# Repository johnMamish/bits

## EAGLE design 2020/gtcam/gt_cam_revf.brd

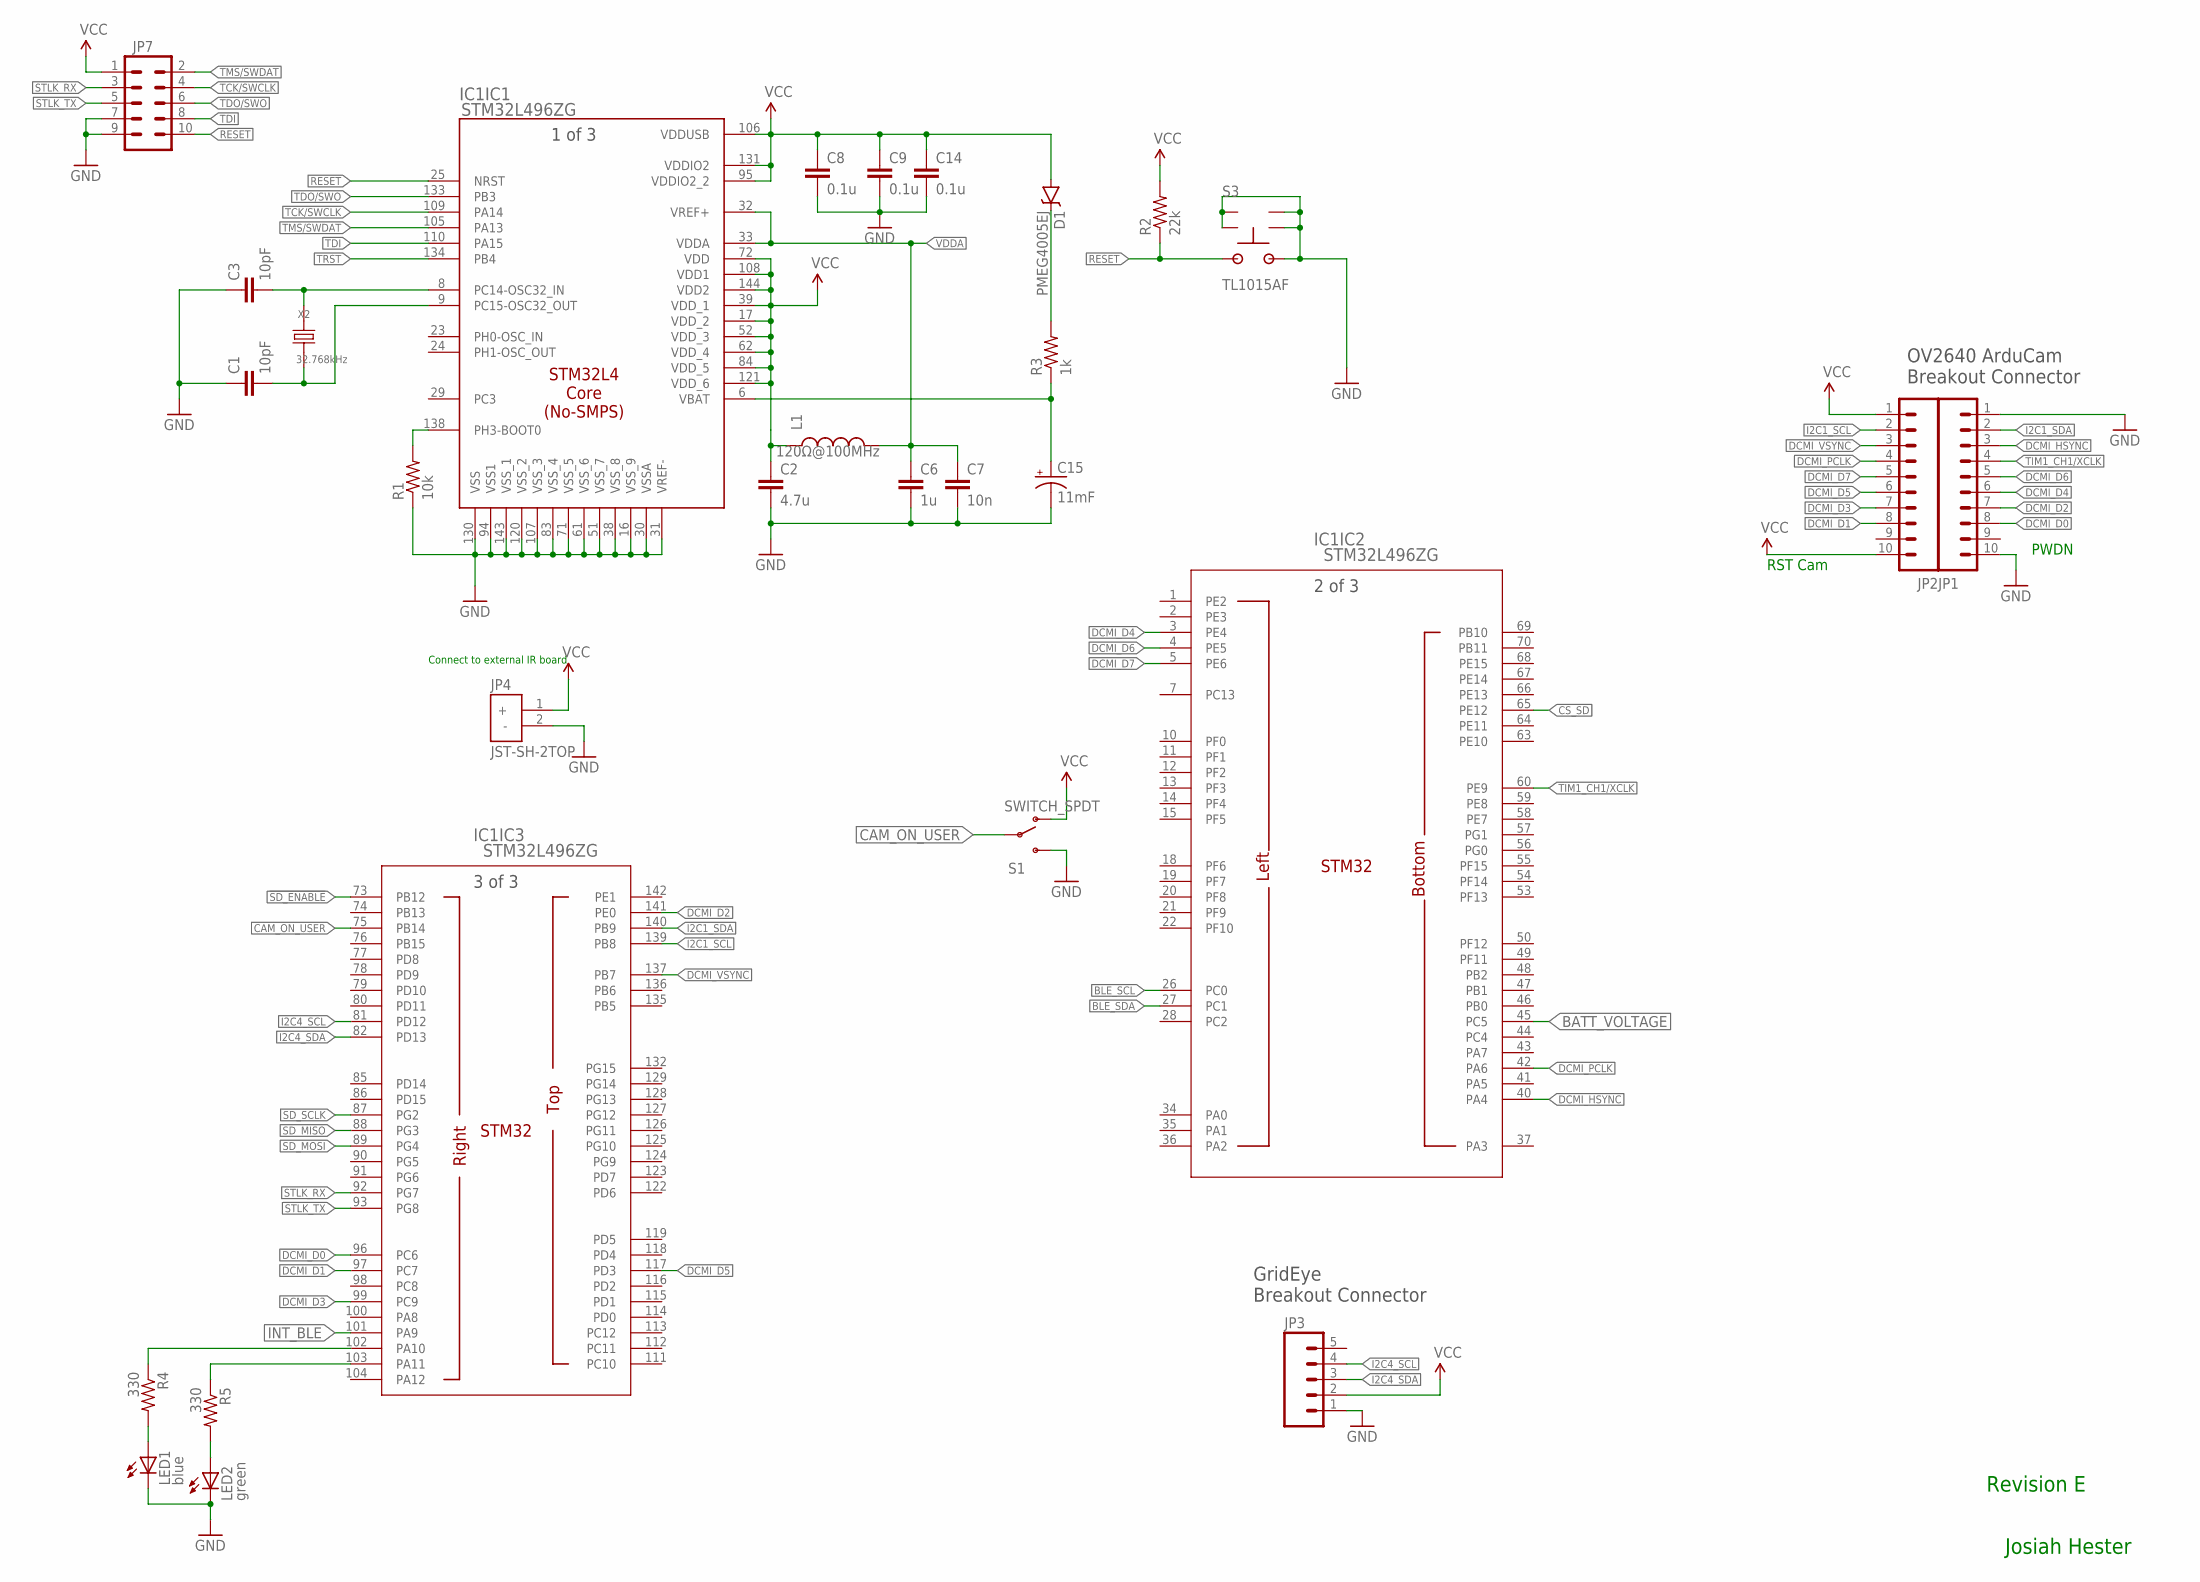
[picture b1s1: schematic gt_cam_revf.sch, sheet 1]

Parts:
C1, C3: 10pF; 0603
C2: 4.7u; 0805
C6: 1u; 0603
C7: 10n; 0603
C8, C9, C14: 0.1u; 0603
C15: 11mF; EIA3216; DIGIKEY 728-1067-1-ND
D1: PMEG4005EJ; SOD-323
IC1: STM32L496ZG; LQFP144-20X20MM; DIGIKEY 497-17999-ND
JP1, JP2: M10SILK_FEMALE_PTH; 1X10
JP3: M05LOCK; 1X05_LOCK
JP4: JST-SH-2TOP; JST-SH-2-TOP
JP7: M05X21.27MM; 2X5_1.27MM; DIGIKEY 1175-1627-ND
L1: 120Ω@100MHz; 0402; DIGIKEY 490-4000-1-ND
LED1: blue; LED-0603
LED2: green; LED-0603
R1: 10k; 0603
R2: 22k; 0603
R3: 1k; 0603
R4, R5: 330; 0603
S1: SWITCH_SPDT; EG-1213
S3: TL1015AF; TS1015; MPN TL1015AF160QG
X2: 32.768kHz; FC-135_1PRIMARY

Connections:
!CS_SD: IC1.65 (PE12); also elsewhere on the board
!SD_ENABLE: IC1.73 (PB12); also elsewhere on the board
BATT_VOLTAGE: IC1.45 (PC5); also elsewhere on the board
BLE_SCL: IC1.26 (PC0); also elsewhere on the board
BLE_SDA: IC1.27 (PC1); also elsewhere on the board
CAM_ON_USER: IC1.75 (PB14), S1.C
DCMI_D0: IC1.96 (PC6), JP1.8
DCMI_D1: IC1.97 (PC7), JP2.8
DCMI_D2: IC1.141 (PE0), JP1.7
DCMI_D3: IC1.99 (PC9), JP2.7
DCMI_D4: IC1.3 (PE4), JP1.6
DCMI_D5: IC1.117 (PD3), JP2.6
DCMI_D6: IC1.4 (PE5), JP1.5
DCMI_D7: IC1.5 (PE6), JP2.5
DCMI_HSYNC: IC1.40 (PA4), JP1.3
DCMI_PCLK: IC1.42 (PA6), JP2.4
DCMI_VSYNC: IC1.137 (PB7), JP2.3
GND: C1.1, C2.2, C3.1, C6.2, C7.2, C8.2, C9.2, C14.2, C15.C (-), IC1.16 (VSS_9), IC1.30 (VSSA), IC1.31 (VREF-), IC1.38 (VSS_8), IC1.51 (VSS_7), IC1.61 (VSS_6), IC1.71 (VSS_5), IC1.83 (VSS_4), IC1.94 (VSS1), IC1.107 (VSS_3), IC1.120 (VSS_2), IC1.130 (VSS), IC1.143 (VSS_1), JP1.1, JP1.10, JP3.1, JP4.2 (-), JP7.7, JP7.9, LED1.C, LED2.C, R1.1, S1.S, S3.1, S3.G1 (GND), S3.G2 (GND), S3.G3 (GND), S3.G4 (GND); also elsewhere on the board
I2C1_SCL: IC1.139 (PB8), JP2.2
I2C1_SDA: IC1.140 (PB9), JP1.2
I2C4_SCL: IC1.81 (PD12), JP3.4
I2C4_SDA: IC1.82 (PD13), JP3.3
INT_BLE: IC1.101 (PA9); also elsewhere on the board
unnamed: C3.2, IC1.8 (PC14-OSC32_IN), X2.2
unnamed: C1.2, IC1.9 (PC15-OSC32_OUT), X2.1
unnamed: IC1.138 (PH3-BOOT0), R1.2
unnamed: D1.C, R3.2
unnamed: IC1.103 (PA11), R5.1
unnamed: IC1.102 (PA10), R4.1
unnamed: LED1.A, R4.2
unnamed: LED2.A, R5.2
RESET: IC1.25 (NRST), JP7.10, R2.1, S3.2
RTC_VBAT: C15.A (+), IC1.6 (VBAT), R3.1
SD_MISO: IC1.88 (PG3); also elsewhere on the board
SD_MOSI: IC1.89 (PG4); also elsewhere on the board
SD_SCLK: IC1.87 (PG2); also elsewhere on the board
STLK_RX: IC1.92 (PG7), JP7.3
STLK_TX: IC1.93 (PG8), JP7.5
TCK/SWCLK: IC1.109 (PA14), JP7.4
TDI: IC1.110 (PA15), JP7.8
TDO/SWO: IC1.133 (PB3), JP7.6
TIM1_CH1/XCLK: IC1.60 (PE9), JP1.4
TMS/SWDAT: IC1.105 (PA13), JP7.2
TRST: IC1.134 (PB4)
VCC: C2.1, C8.1, C9.1, C14.1, D1.A, IC1.17 (VDD_2), IC1.39 (VDD_1), IC1.52 (VDD_3), IC1.62 (VDD_4), IC1.72 (VDD), IC1.84 (VDD_5), IC1.95 (VDDIO2_2), IC1.106 (VDDUSB), IC1.108 (VDD1), IC1.121 (VDD_6), IC1.131 (VDDIO2), IC1.144 (VDD2), JP2.1, JP2.10, JP3.2, JP4.1 (+), JP7.1, L1.1, R2.2, S1.P (O); also elsewhere on the board
VDDA: C6.1, C7.1, IC1.32 (VREF+), IC1.33 (VDDA), L1.2

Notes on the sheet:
OV2640 ArduCam Breakout Connector
GridEye Breakout Connector
Revision E
Josiah Hester
PWDN
RST Cam
Connect to external IR board

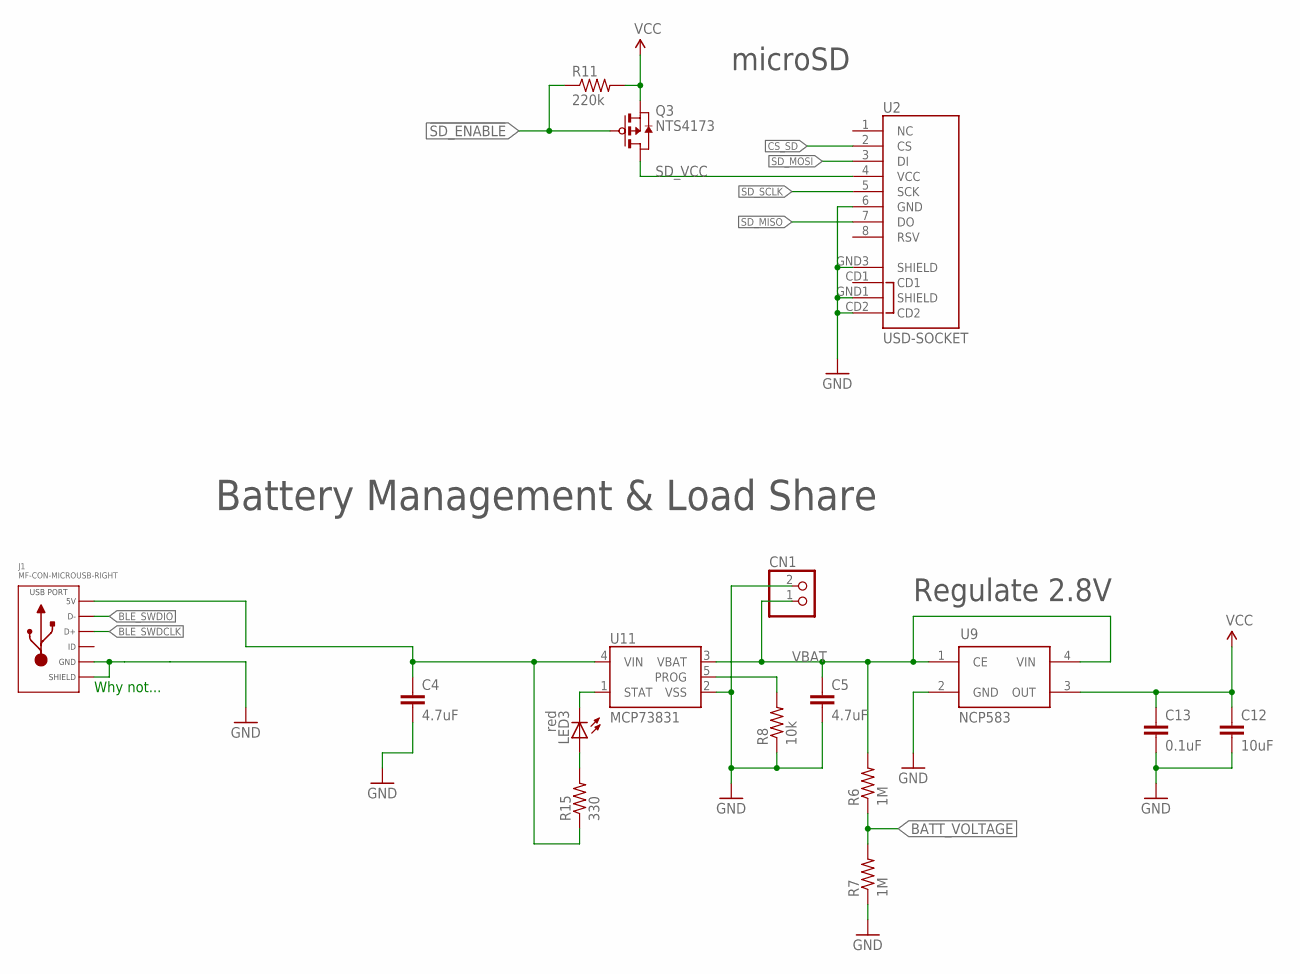
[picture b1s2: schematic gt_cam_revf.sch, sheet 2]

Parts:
C4, C5: 4.7uF; 0805
C12: 10uF; 0805
C13: 0.1uF; 0603
CN1: JST_2PIN-SMT-RA; JST-PH-2-SMT-RA
J1: MF-CON-MICROUSB-RIGHT; MICROUSB-RIGHT
LED3: red; LED-0603
Q3: NTS4173; SC-70-3
R6, R7: 1M; 0603
R8: 10k; 0603
R11: 220k; 0603; DIGIKEY RHM12.0KCDCT-ND
R15: 330; 0603
U2: USD-SOCKET; MICROSD_1:1; DIGIKEY WM3290CT-ND
U9: NCP583; SC82-AB_1PRIMARY
U11: MCP73831; SOT23-5

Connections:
!CS_SD: U2.2 (CS); also elsewhere on the board
!SD_ENABLE: Q3.P1 (G), R11.1; also elsewhere on the board
BATT_VOLTAGE: R6.1, R7.2; also elsewhere on the board
BLE_SWDCLK: J1.3 (D+); also elsewhere on the board
BLE_SWDIO: J1.2 (D-); also elsewhere on the board
GND: C4.2, C5.2, C12.2, C13.2, CN1.2 (1), J1.5 (GND), J1.S1 (SLD), J1.S2 (SLD), J1.S3 (SLD), J1.S4 (SLD), J1.S5 (SLD), J1.S6 (SLD), R7.1, R8.1, U2.6 (GND), U2.CD2, U2.GND1 (SHIELD), U2.GND3 (SHIELD), U9.2 (GND), U11.2 (VSS); also elsewhere on the board
MOB: C4.1, J1.1 (5V), R15.1, U11.4 (VIN)
unnamed: R8.2, U11.5 (PROG)
unnamed: LED3.C, U11.1 (STAT)
unnamed: LED3.A, R15.2
SD_MISO: U2.7 (DO); also elsewhere on the board
SD_MOSI: U2.3 (DI); also elsewhere on the board
SD_SCLK: U2.5 (SCK); also elsewhere on the board
SD_VCC: Q3.P3 (D), U2.4 (VCC)
VBAT: C5.1, CN1.1 (2), R6.2, U9.1 (CE), U9.4 (VIN), U11.3 (VBAT)
VCC: C12.1, C13.1, Q3.P2 (S), R11.2, U9.3 (OUT); also elsewhere on the board

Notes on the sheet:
Regulate 2.8V
Battery Management & Load Share
microSD
Why not...

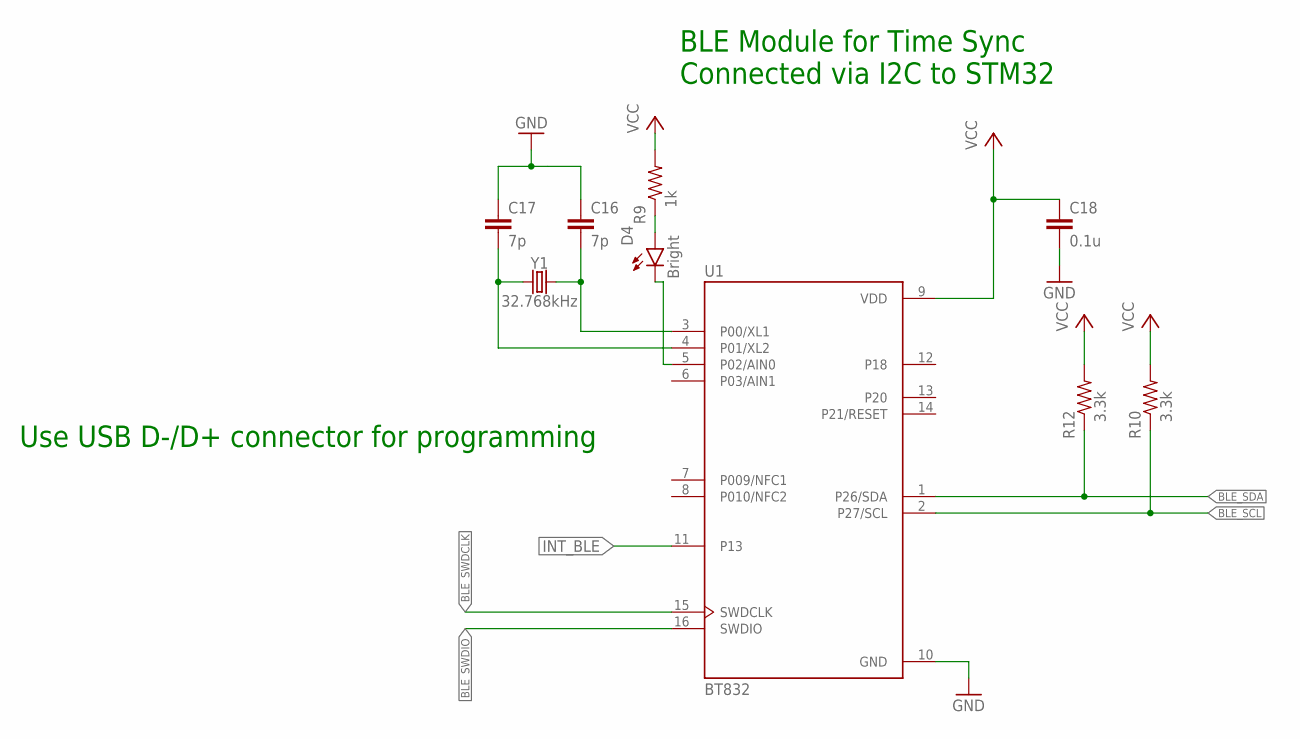
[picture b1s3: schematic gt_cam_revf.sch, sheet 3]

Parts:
C16, C17: 7p; 0603
C18: 0.1u; 0603
D4: Bright; LED-0603
R9: 1k; 0603
R10, R12: 3.3k; 0603
U1: BT832; BLEMODULE_BT832
Y1: 32.768kHz; CRYSTAL-SMD-3.2X1.5MM

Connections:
BLE_SCL: R10.1, U1.2 (P27/SCL); also elsewhere on the board
BLE_SDA: R12.1, U1.1 (P26/SDA); also elsewhere on the board
BLE_SWDCLK: U1.15 (SWDCLK); also elsewhere on the board
BLE_SWDIO: U1.16 (SWDIO); also elsewhere on the board
GND: C16.1, C17.1, C18.2, U1.10 (GND); also elsewhere on the board
INT_BLE: U1.11 (P13); also elsewhere on the board
unnamed: D4.A, R9.1
unnamed: D4.C, U1.5 (P02/AIN0)
unnamed: C16.2, U1.3 (P00/XL1), Y1.P$2 (2)
unnamed: C17.2, U1.4 (P01/XL2), Y1.P$1 (1)
VCC: C18.1, R9.2, R10.2, R12.2, U1.9 (VDD); also elsewhere on the board

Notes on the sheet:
BLE Module for Time Sync Connected via I2C to STM32
Use USB D-/D+ connector for programming

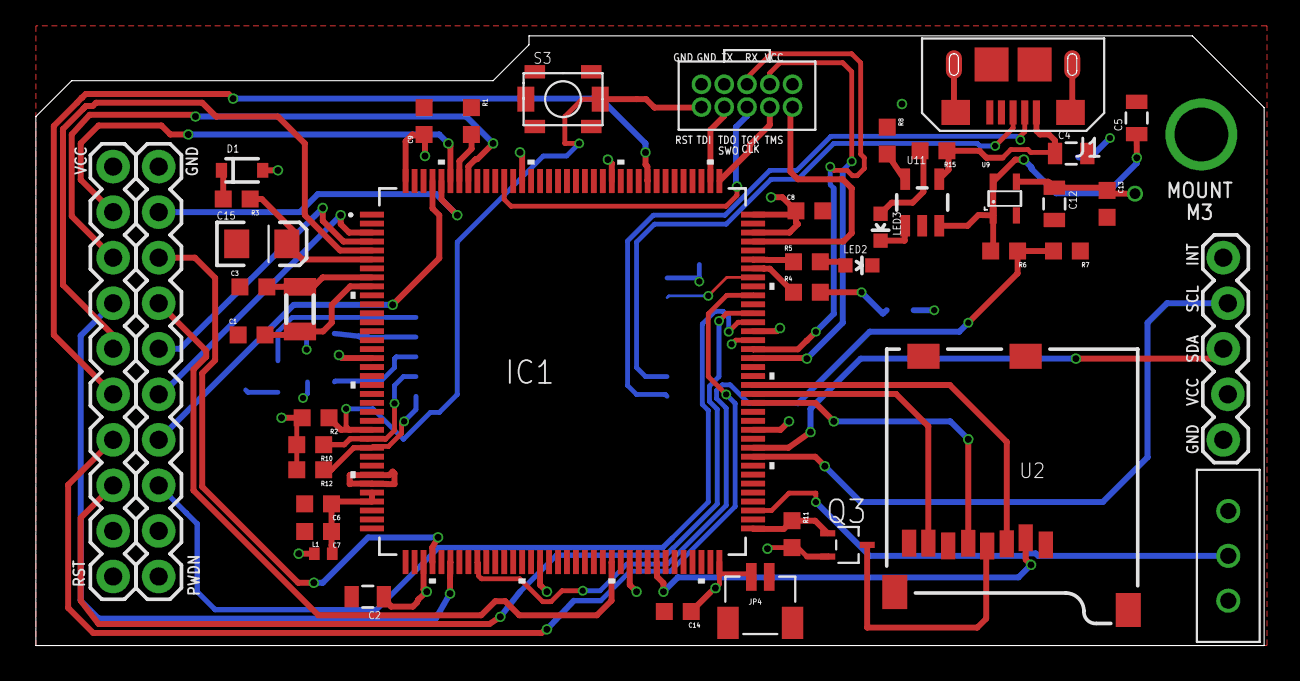
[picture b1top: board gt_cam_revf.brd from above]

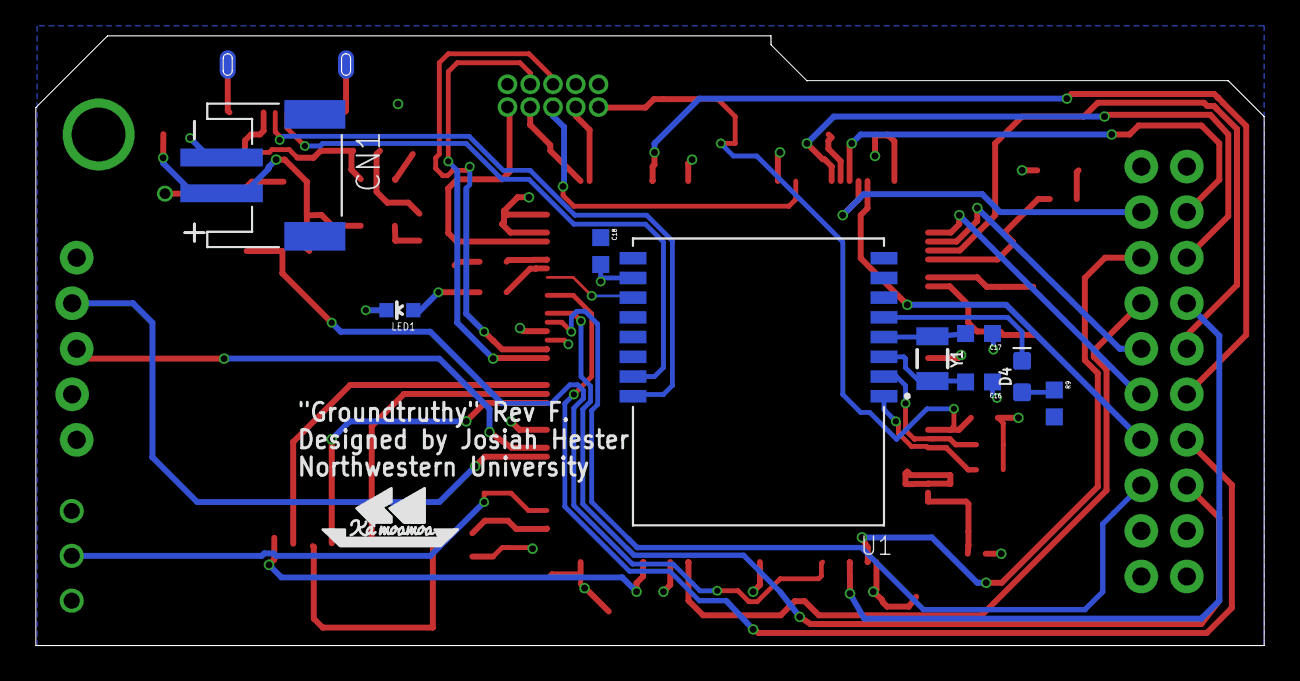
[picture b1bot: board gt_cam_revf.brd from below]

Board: 2 copper layers, 68.5 x 34.0 mm, 53 parts (10 on the bottom side), 57 nets.

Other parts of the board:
U$1: KAMOAMOA

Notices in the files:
parts and their libraries:
SparkFun-Connectors: Licensing: Creative Commons ShareAlike 4.0 International - https://creativecommons.org/licenses/by-sa/4.0
SparkFun-LED: Licensing: CC v3.0 Share-Alike You are welcome to use this library for commercial purposes.
